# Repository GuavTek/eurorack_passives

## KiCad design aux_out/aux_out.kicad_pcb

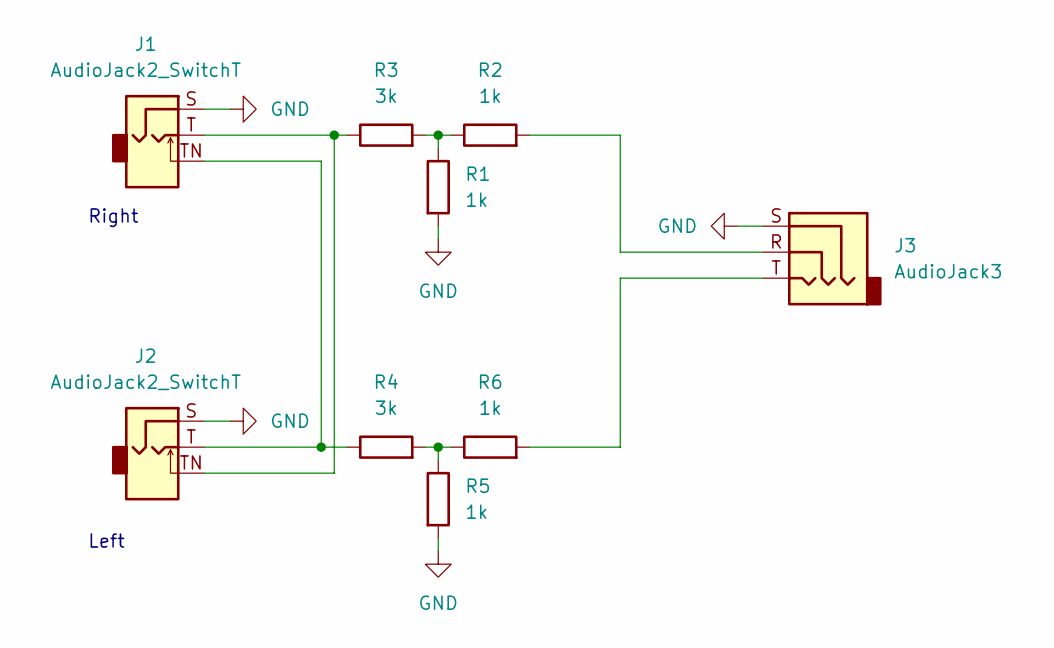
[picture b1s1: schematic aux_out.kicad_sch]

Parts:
J1, J2: AudioJack2_SwitchT; PJ398SM
J3: AudioJack3; PJ366ST
R1, R2, R5, R6: 1k; R_0603_1608Metric
R3, R4: 3k; R_0603_1608Metric

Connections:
GND: J1.S, J2.S, J3.S, R1.2, R5.2
unnamed: J1.T, J2.TN, R3.1
unnamed: J1.TN, J2.T, R4.1
unnamed: J3.R, R2.2
unnamed: J3.T, R6.2
unnamed: R1.1, R2.1, R3.2
unnamed: R4.2, R5.1, R6.1

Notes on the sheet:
Right
Left

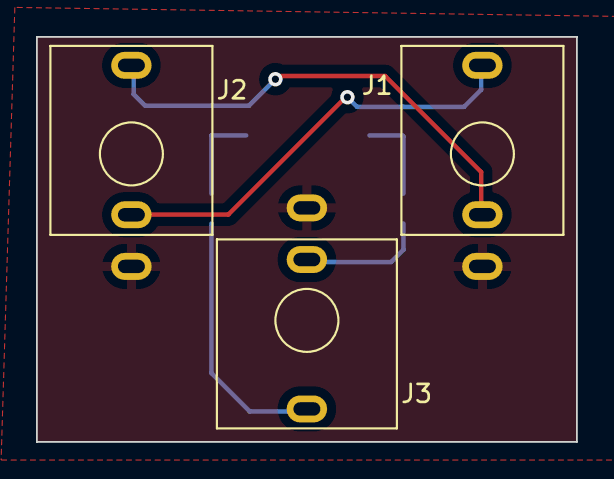
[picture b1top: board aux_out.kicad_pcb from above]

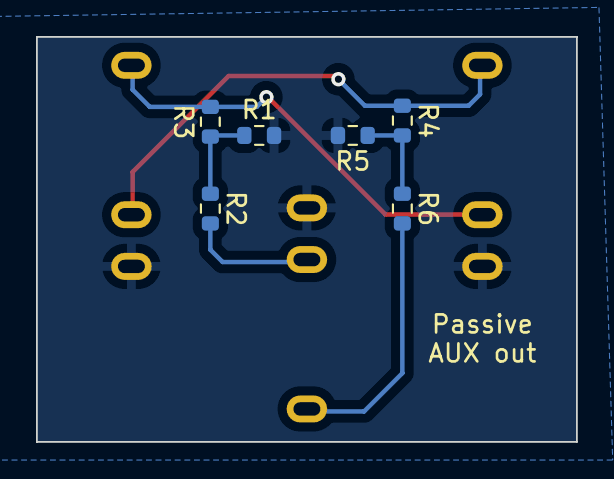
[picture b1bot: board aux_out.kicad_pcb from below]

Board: 2 copper layers, 30.0 x 22.5 mm, 9 parts (6 on the bottom side), 7 nets.
